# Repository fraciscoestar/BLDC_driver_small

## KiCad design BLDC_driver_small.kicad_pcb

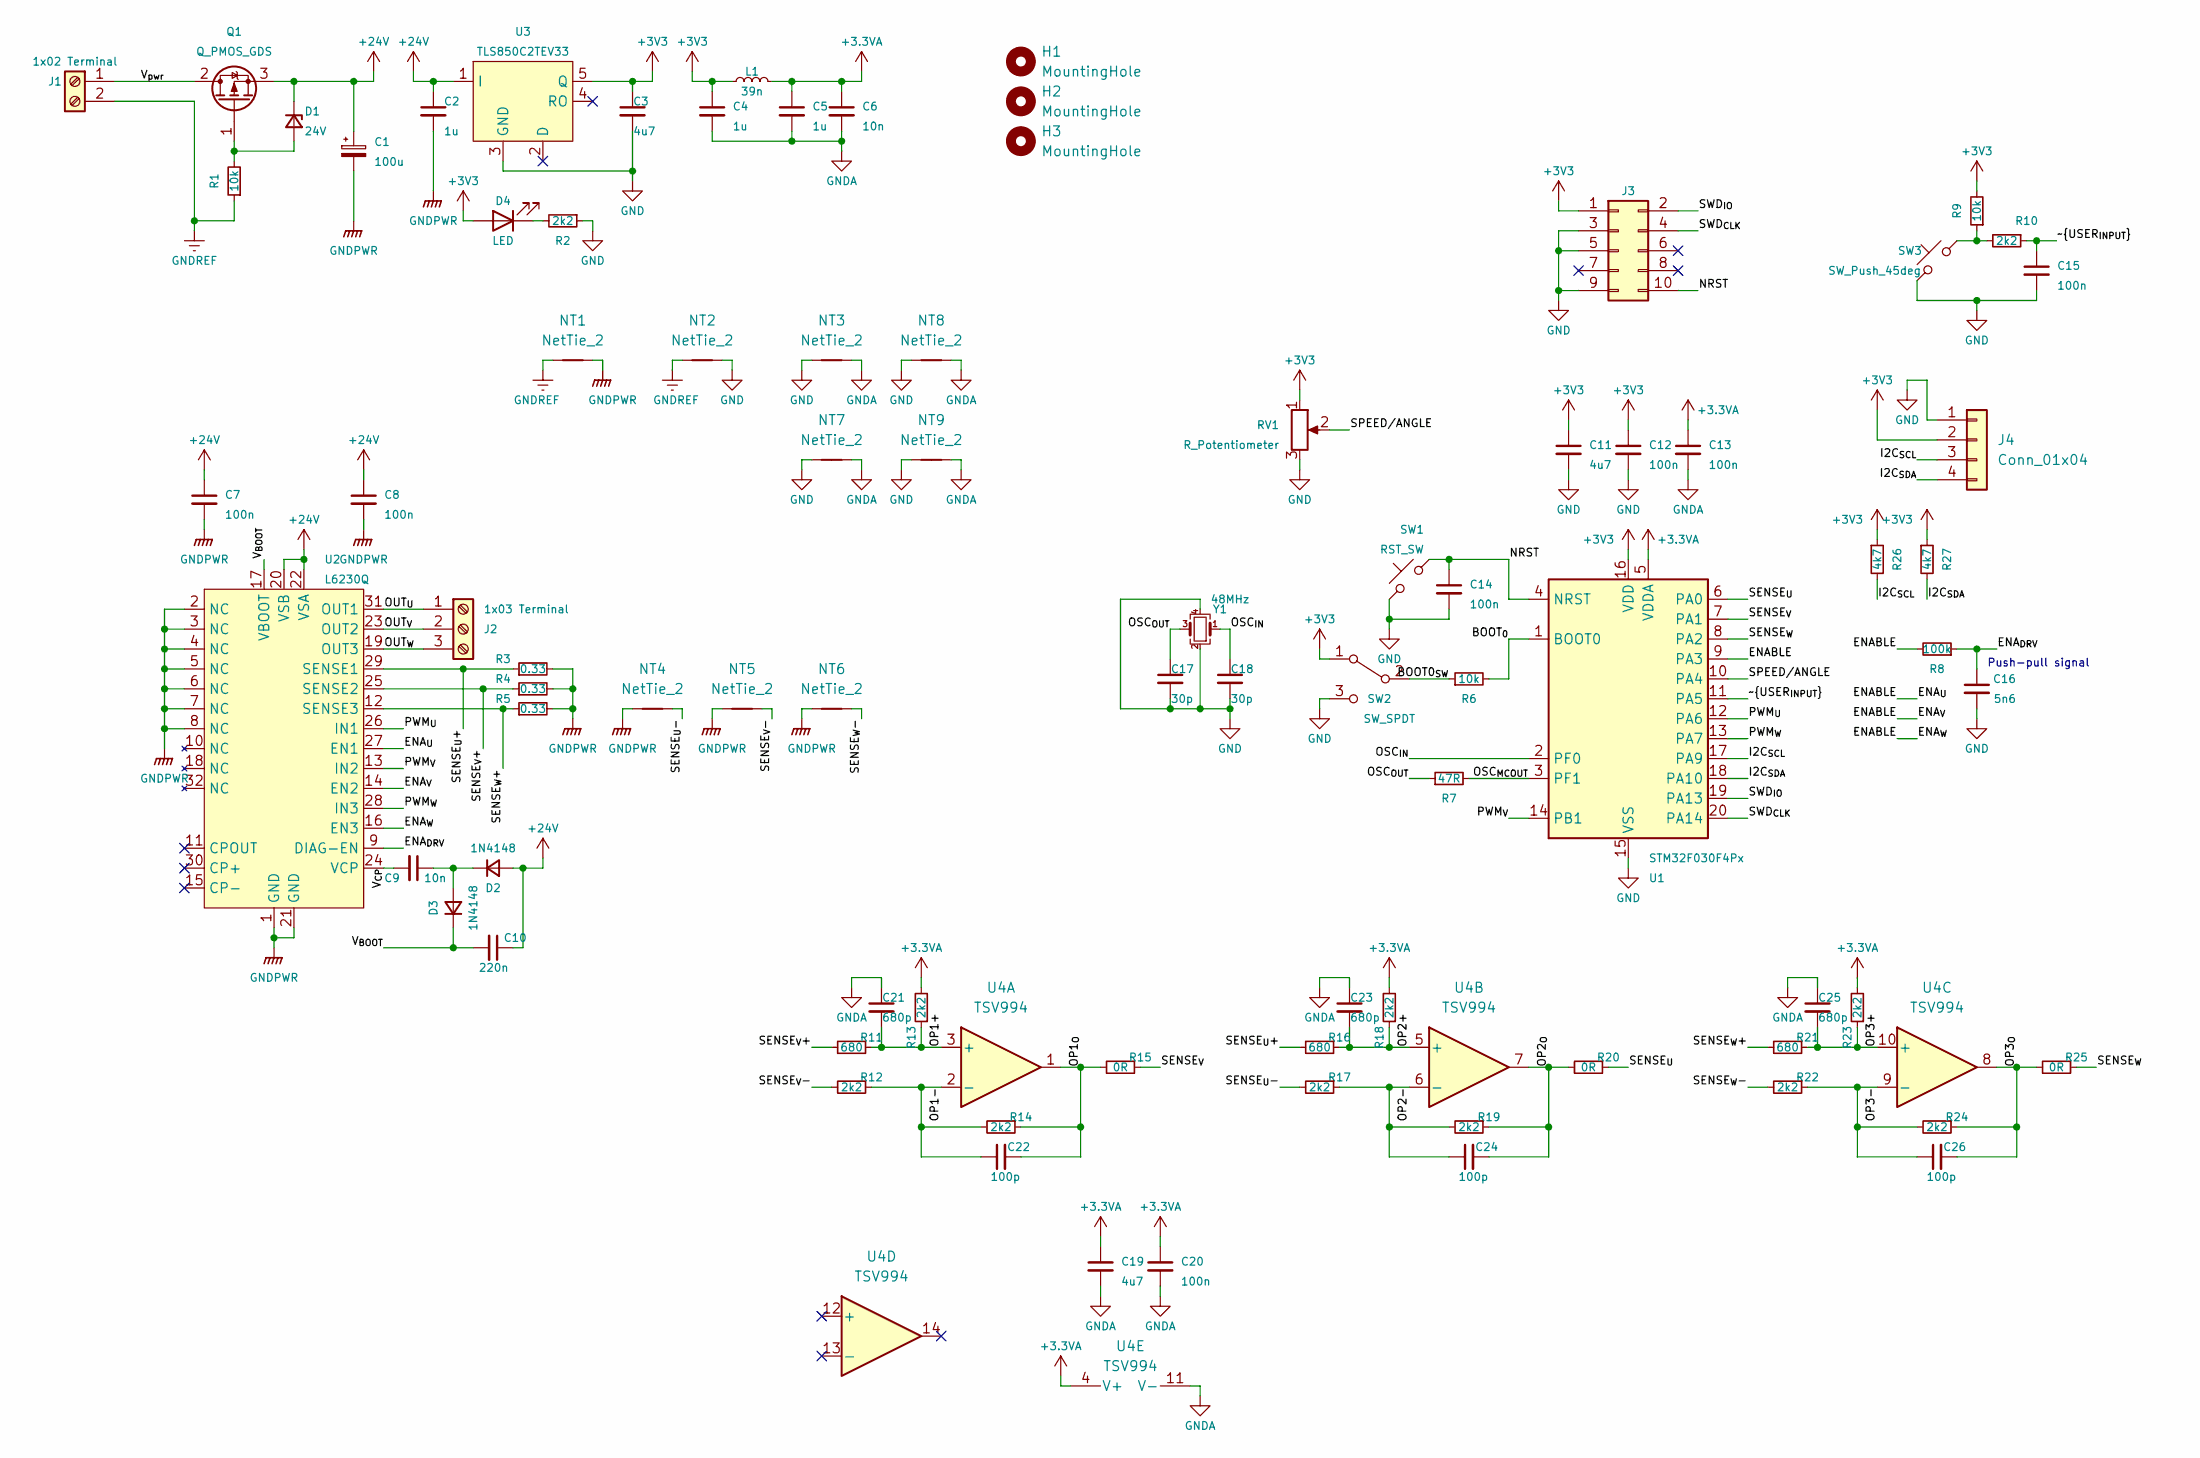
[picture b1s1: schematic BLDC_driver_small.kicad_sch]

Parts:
C1: 100u; CP_Elec_10x10.5; MPN 865060757007
C2: 1u; C_0603_1608Metric; MPN UMK107BJ105KA-T
C3: 4u7; C_0603_1608Metric; MPN GRM188R6YA475KE15J
C4, C5: 1u; C_0402_1005Metric; MPN EMK105BJ105KV8F
C6, C9: 10n; C_0402_1005Metric; MPN UMK105B7103KV-F
C7, C8, C12, C13, C14, C15, C20: 100n; C_0402_1005Metric; MPN 885012205092
C10: 220n; C_0402_1005Metric; MPN TMK105B7224KV-FR
C11, C19: 4u7; C_0402_1005Metric; MPN GRM155C61E475ME15J
C16: 5n6; C_0402_1005Metric; MPN GRM155R71E562JA01D
C17, C18: 30p; C_0402_1005Metric; MPN 04025A300FAT2A
C21, C23, C25: 680p; C_0402_1005Metric; MPN MAASH105SB7681KFCA01
C22, C24, C26: 100p; C_0402_1005Metric; MPN C0402C101K3RACAUTO
D1: 24V; D_SOD-123; MPN MMSZ5252C-G3-08
D2, D3: 1N4148; D_SOD-523; MPN 1N4148X-TP
D4: LED; LED_0603_1608Metric; MPN 150060GS75000
H1, H2, H3: MountingHole; MountingHole_2.2mm_M2
J1: 1x02 Terminal; TerminalBlock_Altech_AK300-2_P5.00mm; MPN 1711026
J2: 1x03 Terminal; TerminalBlock_Altech_AK300-3_P5.00mm; MPN 1711039
J3: Conn_02x05_Odd_Even; PinHeader_2x05_P2.54mm_Vertical; MPN 5103310-1
J4: Conn_01x04; PinHeader_1x04_P2.54mm_Vertical; MPN 90147-1204
L1: 39n; L_0603_1608Metric; MPN LQG18HN39NJ00D
NT1, NT2: NetTie_2; NetTie-2_SMD_Pad2.0mm
NT3, NT4, NT5, NT6, NT7, NT8, NT9: NetTie_2; NetTie-2_SMD_Pad0.5mm
Q1: Q_PMOS_GDS; SOT-23; MPN SQ2319ADS-T1_BE3
R1, R6, R9: 10k; R_0402_1005Metric; MPN ERJ-2RKF1002X
R2, R10, R12, R13, R14, R17, R18, R19, R22, R23, R24: 2k2; R_0402_1005Metric; MPN ERJ-2RKF2201X
R3, R4, R5: 0.33; R_1210_3225Metric; MPN RCWE1210R330FKEA
R7: 47R; R_0402_1005Metric; MPN ERJ-2RKF47R0X
R8: 100k; R_0402_1005Metric; MPN ERJ-2RKF1003X
R11, R16, R21: 680; R_0402_1005Metric; MPN ERJ-2RKF6800X
R15, R20, R25: 0R; R_0402_1005Metric; MPN ERJ-2GE0R00X
R26, R27: 4k7; R_0402_1005Metric; MPN ERJ-2RKF4701X
RV1: R_Potentiometer; Potentiometer_Bourns_3314S_Horizontal; MPN 3314J-1-204E
SW1: RST_SW; SW_SPST_B3S-1000; MPN K2-1157SP-B3SW-01
SW2: SW_SPDT; SW_SPDT_PCM12; MPN SK-3296S-01-L1
SW3: SW_Push_45deg; SW_SPST_B3S-1000; MPN K2-1157SP-B3SW-01
U1: STM32F030F4Px; TSSOP-20_4.4x6.5mm_P0.65mm; MPN STM32F030F4P6
U2: L6230Q; VFQFPN32; MPN L6230Q
U3: TLS850C2TEV33; PG-TO252-5; MPN TLS850C2TEV33
U4: TSV994; TSSOP-14_4.4x5mm_P0.65mm; MPN TSV994
Y1: 48MHz; Crystal_SMD_3225-4Pin_3.2x2.5mm; MPN 7B048000R01

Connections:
+3.3VA: C5.1, C6.1, C13.1, C19.1, C20.1, L1.2, R13.2, R18.2, R23.2, U1.5 (VDDA), U4.4 (V+)
+3V3: C3.1, C4.1, C11.1, C12.1, D4.2 (A), J3.1, J4.2, L1.1, R9.2, R26.1, R27.1, RV1.1, SW2.1 (A), U1.16 (VDD), U3.5 (Q)
+24V: C1.1, C2.1, C7.1, C8.1, C10.1, D1.1 (K), D2.2 (A), Q1.3 (S), U2.20 (VSB), U2.22 (VSA), U3.1 (I)
/BOOT0_{SW}: R6.1, SW2.2 (B)
/BOOT_{0}: R6.2, U1.1 (BOOT0)
/ENABLE: R8.2, U1.9 (PA3), U2.14 (EN2), U2.16 (EN3), U2.27 (EN1)
/ENA_{DRV}: C16.1, R8.1, U2.9 (DIAG-EN)
/I2C_{SCL}: J4.3, R26.2, U1.17 (PA9)
/I2C_{SDA}: J4.4, R27.2, U1.18 (PA10)
/NRST: C14.1, J3.10, SW1.2, U1.4 (NRST)
/OP1+: C21.2, R11.1, R13.1, U4.3 (+)
/OP1-: C22.1, R12.1, R14.2, U4.2 (-)
/OP1_{O}: C22.2, R14.1, R15.2, U4.1
/OP2+: C23.2, R16.1, R18.1, U4.5 (+)
/OP2-: C24.1, R17.1, R19.2, U4.6 (-)
/OP2_{O}: C24.2, R19.1, R20.2, U4.7
/OP3+: C25.2, R21.1, R23.1, U4.10 (+)
/OP3-: C26.1, R22.1, R24.2, U4.9 (-)
/OP3_{O}: C26.2, R24.1, R25.2, U4.8
/OSC_{IN}: C18.1, U1.2 (PF0), Y1.1
/OSC_{MCOUT}: R7.2, U1.3 (PF1)
/OSC_{OUT}: C17.1, R7.1, Y1.3
/OUT_{U}: J2.1, U2.31 (OUT1)
/OUT_{V}: J2.2, U2.23 (OUT2)
/OUT_{W}: J2.3, U2.19 (OUT3)
/PWM_{U}: U1.12 (PA6), U2.26 (IN1)
/PWM_{V}: U1.14 (PB1), U2.13 (IN2)
/PWM_{W}: U1.13 (PA7), U2.28 (IN3)
/SENSE_{U}: R20.1, U1.6 (PA0)
/SENSE_{U}+: R3.1, R16.2, U2.29 (SENSE1)
/SENSE_{U}-: NT4.2, R17.2
/SENSE_{V}: R15.1, U1.7 (PA1)
/SENSE_{V}+: R4.1, R11.2, U2.25 (SENSE2)
/SENSE_{V}-: NT5.2, R12.2
/SENSE_{W}: R25.1, U1.8 (PA2)
/SENSE_{W}+: R5.1, R21.2, U2.12 (SENSE3)
/SENSE_{W}-: NT6.2, R22.2
/SPEED/ANGLE: RV1.2, U1.10 (PA4)
/SWD_{CLK}: J3.4, U1.20 (PA14)
/SWD_{IO}: J3.2, U1.19 (PA13)
/V_{BOOT}: C10.2, D3.1 (K), U2.17 (VBOOT)
/V_{CP}: C9.2, U2.24 (VCP)
/V_{pwr}: J1.1, Q1.2 (D)
/~USER_{INPUT}: C15.1, R10.1, U1.11 (PA5)
GND: C3.2, C11.2, C12.2, C14.2, C15.2, C16.2, C17.2, C18.2, J3.3, J3.5, J3.9, J4.1, NT2.2, NT3.1, NT7.1, NT8.1, NT9.1, R2.1, RV1.3, SW1.1, SW2.3 (C), SW3.1, U1.15 (VSS), U3.3 (GND), Y1.2, Y1.4
GNDA: C4.2, C5.2, C6.2, C13.2, C19.2, C20.2, C21.1, C23.1, C25.1, NT3.2, NT7.2, NT8.2, NT9.2, U4.11 (V-)
GNDPWR: C1.2, C2.2, C7.2, C8.2, NT1.2, NT4.1, NT5.1, NT6.1, R3.2, R4.2, R5.2, U2.1 (GND), U2.2 (NC), U2.3 (NC), U2.4 (NC), U2.5 (NC), U2.6 (NC), U2.7 (NC), U2.8 (NC), U2.21 (GND)
GNDREF: J1.2, NT1.1, NT2.1, R1.1
unnamed: C9.1, D2.1 (K), D3.2 (A)
unnamed: D1.2 (A), Q1.1 (G), R1.2
unnamed: D4.1 (K), R2.2
unnamed: R9.1, R10.2, SW3.2

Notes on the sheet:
Push-pull signal

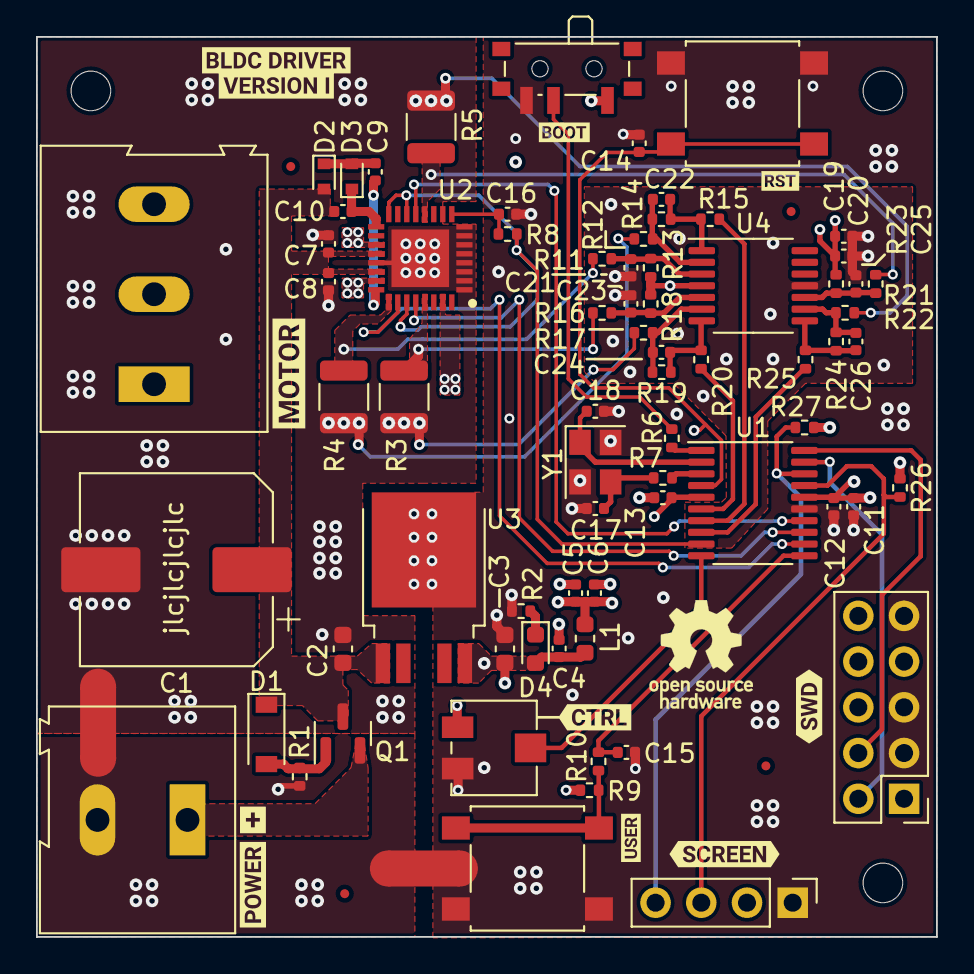
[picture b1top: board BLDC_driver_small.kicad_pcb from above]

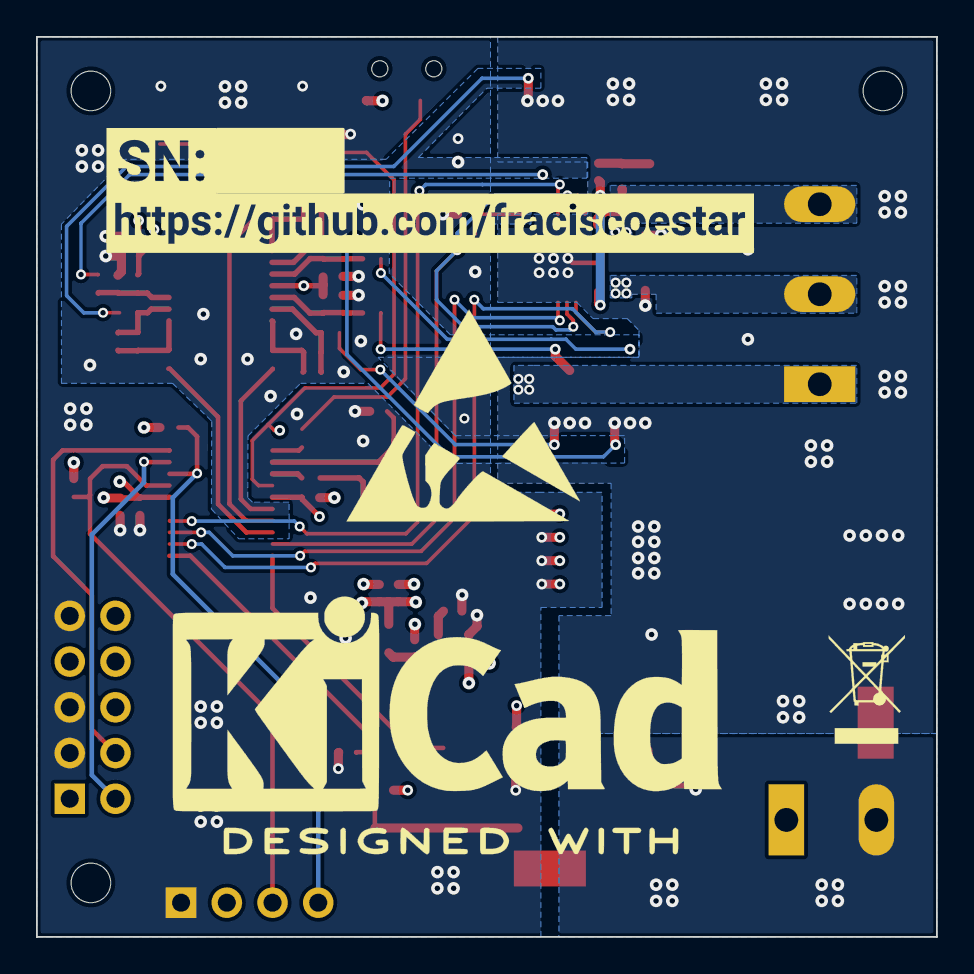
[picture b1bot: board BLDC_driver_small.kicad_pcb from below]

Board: 6 copper layers, 50.0 x 50.0 mm, 97 parts (2 on the bottom side), 52 nets.

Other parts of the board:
kibuzzard-641818A1: G***; kibuzzard-641818A1
kibuzzard-641842DD: G***; kibuzzard-641842DD
kibuzzard-641842EC: G***; kibuzzard-641842EC
kibuzzard-641877D0: G***; kibuzzard-641877D0
kibuzzard-641879B1: G***; kibuzzard-641879B1
kibuzzard-6418180F: G***; kibuzzard-6418180F
kibuzzard-6418190C: G***; kibuzzard-6418190C
kibuzzard-6418363F: G***; kibuzzard-6418363F
kibuzzard-64181824: G***; kibuzzard-64181824
kibuzzard-64183623: G***; kibuzzard-64183623
kibuzzard-64183651: G***; kibuzzard-64183651
kibuzzard-64183661: G***; kibuzzard-64183661
kibuzzard-64183696: G***; kibuzzard-64183696

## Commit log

2023-03-12 120323
2023-03-12 120223-2
2023-03-13 130323
2023-03-13 130323-2
2023-03-13 130323-3 fullchange
2023-03-14 140323
2023-03-15 150323
2023-03-15 160323
2023-03-16 160323-2
2023-03-17 170323-v1.0
2023-03-19 190323
2023-03-19 v190323-2
2023-03-20 200323-final
2023-03-20 v1.0
2023-03-20 Create License
